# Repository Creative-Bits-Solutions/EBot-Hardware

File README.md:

# EBot-Hardware
EBot is a DIY ecosystem developed for students, kids, artists, and robotics enthusiasts to learn, explore and build working prototypes through experiments and games. Entire system includes an electronic development board with wide range of compactable sensors, graphical programming software based on Google Blockly, bunch of wheels, gears, motors, shafts and plastics, books and study materials that help to learn all basic concepts of mechanical designing, programing and electronic prototyping

We focus on STEM education to improve imagination, reasoning, analytical thinking and problem solving skills of kids. Let them Play, Make and Learn with EBot system.

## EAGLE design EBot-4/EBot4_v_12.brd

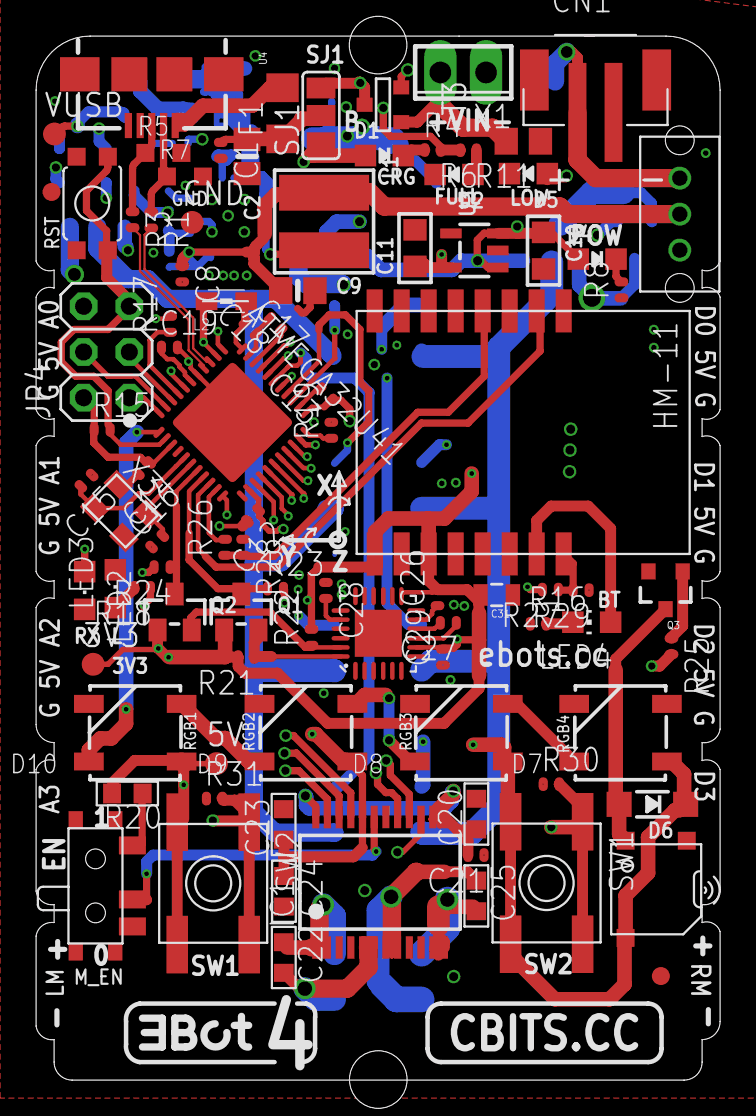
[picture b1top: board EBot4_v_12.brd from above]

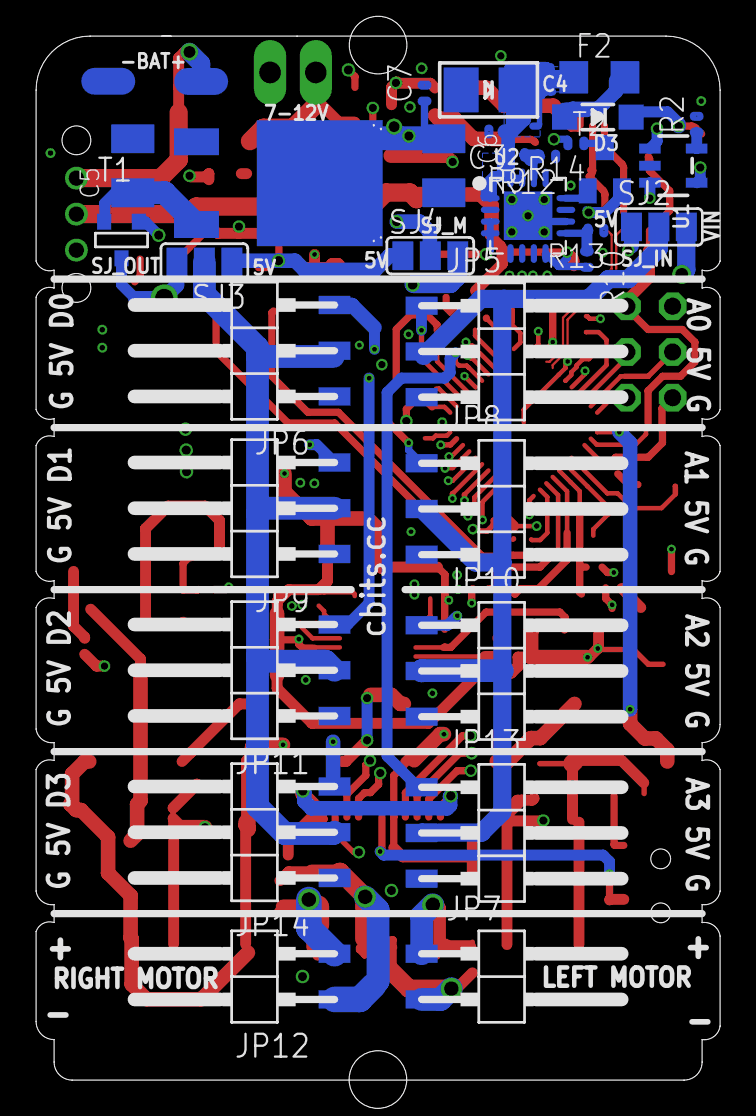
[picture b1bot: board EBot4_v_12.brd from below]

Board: 4 copper layers, 38.0 x 58.0 mm, 126 parts (33 on the bottom side), 84 nets.

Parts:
3V3, 5V: TPB1,27; B1,27
ATMEGA32U41: ATMEGA32U4-XUMU; QFN44ML7X7
AZ1084C1: AZ1084C
C1, C7, C12, C13, C14, C18: 100n; C0402
C2: 4.7µF; 0805-NO
C3: 2.2uF; C0402
C4: 100uF/6V; EIA3528-21/B-R
C5, C6: 22u; SMC_B
C8, C21, C26, C27: 0.1uF; C0402
C9: 10uF; 0805-NO
C10, C11: 10µF; _0805
C15, C16: 22pF; C0402
C17, C19: 1uF; C0402
C20, C23: 10uf; C0603
C22, C25: 0.1u; C0603
C24: 0.1uf; C0603
C28: 2.2nF; C0402
C29: 10nF; C0402
C31: 0.1uF; 0805
CN1: JST-PH-2-SMT
D1: YELLOW; CHIPLED_0805_NOOUTLINE
D2: GREEN; CHIPLED_0805_NOOUTLINE
D3, D6: MBR120; SOD-123
D4: red; CHIPLED_0805_NOOUTLINE
D5: RED; CHIPLED_0805_NOOUTLINE
D7, D8, D9, D10: WS2812B
EBOT_LOGO2: EBOT_NAME_6MM
F1, F2: 500mA; R1206
GND: TPB1,27; B1,27
HM-111: HM-11
IC1: TB6612FNG; SSOP24
JP2, JP3: FIDUCIAL1X2; FIDUCIAL-1X2
JP4: 3x2M; 2X03
JP5, JP6, JP8, JP9, JP10, JP11, JP13, JP14: 1X03SMD/90
JP7, JP12: 1X02SMD/90
KMR1: KMR7
L1: VLC5045-6.8uH; INDUCTOR_5X5MM_TDK_VLC5045
L2: MH2029-300Y; 0805
LED2: yellow; CHIPLED_0805
LED3: BLUE; CHIPLED_0805
LED4: CHIP-LED0805
MPU-60501: MPU-6050-1; QFN-24-4MM2
ON_OFF_SLIDE1: OS102011MA1QN1
Q1, Q2: BSS138; SOT23-WIDE@1
Q3: 2222A; SOT23-3
R1, R3: 22R; R0402
R2, R28, R29: 2K; R0402
R4: 470; R0402
R5, R7: CG0603MLC-05E; CT/CN0603
R6, R17, R18, R26, R27, R30, R31: 1K; R0402
R8, R14: 1k; R0402
R9, R10: 1.87M; R0402
R11: 10k; R0805
R12: 200K; R0402
R13: 340K; R0402
R15, R19, R21, R22, R23, R24: 10K; R0402
R16: 330; R0402
R20: 10K; R0603
R25: 270; R0402
SJ1, SJ2, SJ3, SJ4: SJ_2
SK-12C04051: SK-12C0405
SPK1: SMT-0540-S-R
SW1, SW2: SPST_TACT-EVQQ2; EVQ-Q2
T1: PMV48XP; SOT-23
T2: MMUN2133LT1G; SC59-BEC
T3: FDN340P/PMV48XP; SOT-23
U1: MCP73831T-2ACI/OT; SOT23-5
U2: TPS61030RSAR; PVQFN-16
U3: RT9193; SOT23-5@1
U4: USB-AB-MICRO-SMD
U$1, U$2: BATCON
VUSB: TPB1,27; B1,27
X1: 2POL254
X3: 16MHz KX-7; CRYSTAL-3.2-2.5

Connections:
+3V3: 3V3.TP, C11.1, C26.2, C29.2, C31.2, HM-111.RESETB, HM-111.VCC, MPU-60501.8, MPU-60501.13, Q1.1, Q2.1, R21.2, R22.2, U3.5
+5V: 5V.TP, ATMEGA32U41.2, ATMEGA32U41.14, ATMEGA32U41.24, ATMEGA32U41.34, AZ1084C1.VOUT, C6.+, C7.1, C10.1, C12.1, C13.1, C14.1, C23.1, C24.1, D4.A, D6.C, D7.1, D8.1, D9.1, D10.1, IC1.20, JP4.2, L2.1, R15.1, R20.2, R23.2, R24.2, SJ2.1, SJ3.1, SJ4.1, SPK1.-, SW1.A, SW1.A', SW2.A, SW2.A', T1.3, T3.2, U3.1, U3.3
A0: ATMEGA32U41.36, JP5.1
A1: ATMEGA32U41.37, JP8.1
A2: ATMEGA32U41.38, JP10.1
A3: ATMEGA32U41.39, JP13.1
A4: ATMEGA32U41.40, JP11.3
A5: ATMEGA32U41.41, JP14.3
AO1': C22.1, IC1.1, IC1.2, JP7.1
AO2': C22.2, IC1.5, IC1.6, JP7.2
AREF: ATMEGA32U41.42, C18.1
AVCC: ATMEGA32U41.44, C17.1, L2.2
BLE_KEY: HM-111.PIO0, R27.1, R29.2
BLE_LED: HM-111.PIO1, LED4.A
BO1': C25.2, IC1.11, IC1.12, JP12.2
BO2': C25.1, IC1.7, IC1.8, JP12.1
D0/RX: ATMEGA32U41.20, HM-111.UART_TX
D1/TX: ATMEGA32U41.21, R26.2
D4/M1: ATMEGA32U41.25, IC1.22
D5*/PWM2: ATMEGA32U41.31, IC1.15
D6*/PWM1: ATMEGA32U41.27, IC1.23
D7: ATMEGA32U41.1, JP9.3
D+: R3.1, R5.1, U4.D+
D-: R1.1, R7.1, U4.D-
GND: ATMEGA32U41.5, ATMEGA32U41.15, ATMEGA32U41.23, ATMEGA32U41.35, ATMEGA32U41.43, ATMEGA32U41.EXP, AZ1084C1.GND, C1.2, C2.2, C3.2, C4.-, C5.-, C6.-, C7.2, C8.2, C9.2, C10.2, C11.2, C12.2, C13.2, C14.2, C15.1, C16.1, C17.2, C18.2, C19.2, C20.2, C21.1, C23.2, C24.2, C26.1, C27.1, C28.1, C29.1, C31.1, CN1.2, D2.C, D5.C, D7.3, D8.3, D9.3, D10.3, GND.TP, HM-111.GND, IC1.3, IC1.4, IC1.9, IC1.10, IC1.18, JP4.6, JP5.3, JP6.1, JP8.3, JP9.1, JP10.3, JP11.1, JP13.3, JP14.1, KMR1.P$1, KMR1.P$2, LED2.C, LED3.C, MPU-60501.1, MPU-60501.9, MPU-60501.11, MPU-60501.18, Q3.2, R2.2, R5.2, R7.2, R8.1, R11.1, R12.1, R13.1, R16.1, R19.2, R28.1, R29.1, R30.1, R31.1, SK-12C04051.R, U1.2, U2.5, U2.6, U2.7, U2.10, U2.13, U2.P$18, U2.P$19, U2.P$20, U2.P$21, U2.P$22, U2.THERMAL, U3.2, U4.GND, U$2.P$1, X1.1, X3.2, X3.4
HWB: ATMEGA32U41.33, R19.1
IO8: ATMEGA32U41.28, JP6.3
IO9*/M3: ATMEGA32U41.29, IC1.17
IO10*: ATMEGA32U41.30, R25.2
IO11*/RGB: ATMEGA32U41.12, D10.4
IO12*/M4: ATMEGA32U41.26, IC1.21
IO13*: ATMEGA32U41.32, R18.1
LBI: R10.1, R13.2, U2.9
LBO: T2.B, U2.12
M2: ATMEGA32U41.22, IC1.16
MISO: ATMEGA32U41.11, JP4.1, R30.2, SW1.B, SW1.B'
MOSI: ATMEGA32U41.10, JP4.4, R31.2, SW2.B, SW2.B'
unnamed: D1.A, SJ1.1, U1.4
unnamed: LED2.A, R17.2
unnamed: C8.1, C9.1, L1.P$1, ON_OFF_SLIDE1.P$2, R10.2, U2.8
unnamed: LED3.A, R18.2
unnamed: D9.4, D10.2
unnamed: D1.C, R4.1
unnamed: D8.4, D9.2
unnamed: HM-111.UART_RX, R26.1, R28.2
unnamed: JP5.2, JP8.2, JP10.2, JP13.2, SJ2.2
unnamed: C28.2, MPU-60501.20
unnamed: C27.2, MPU-60501.10
unnamed: D7.4, D8.2
unnamed: LED4.C, R16.2
unnamed: R4.2, R6.2, U1.1
unnamed: R2.1, U1.5
unnamed: D2.A, R6.1
unnamed: L1.P$2, U2.3, U2.4
unnamed: D4.C, R8.2
unnamed: D5.A, R14.2
unnamed: R14.1, T2.C
unnamed: D3.A, F2.2
unnamed: JP6.2, JP9.2, JP11.2, JP14.2, SJ3.2
unnamed: Q3.1, R25.1
unnamed: F1.2, U4.VBUS
unnamed: C1.1, C2.1, F1.1, SJ1.2
unnamed: R9.1, R12.2, U2.14
unnamed: D6.A, Q3.3, SPK1.+
unnamed: AZ1084C1.VIN, C5.+, T1.2
unnamed: C20.1, C21.2, IC1.13, IC1.14, IC1.24, SJ4.2
unnamed: R20.1, SK-12C04051.L
RD_N: ATMEGA32U41.3, R1.2
RD_P: ATMEGA32U41.4, R3.2
RESET: ATMEGA32U41.13, JP4.5, KMR1.P$3, KMR1.P$4, R15.2
RXLED/SS: ATMEGA32U41.8, R17.1
SCK: ATMEGA32U41.9, JP4.3, R27.2
SCL_3V: MPU-60501.23, Q2.2, R22.1
SCL_5V: ATMEGA32U41.18, Q2.3, R24.1
SDA_3V: MPU-60501.24, Q1.2, R21.1
SDA_5V: ATMEGA32U41.19, Q1.3, R23.1
STBY: IC1.19, SK-12C04051.M
UCAP: ATMEGA32U41.6, C19.1
V+: CN1.1, ON_OFF_SLIDE1.P$3, U1.3, U$1.P$1
VDD: R11.2, SJ2.3, SJ3.3, SJ4.3, T1.1, T3.3, X1.2
VOUT1: C3.1, C4.+, F2.1, R9.2, U2.1, U2.15, U2.16
VUSB: ATMEGA32U41.7, D3.C, SJ1.3, T3.1, VUSB.TP
XTAL1: ATMEGA32U41.17, C16.2, X3.3
XTAL2: ATMEGA32U41.16, C15.2, X3.1

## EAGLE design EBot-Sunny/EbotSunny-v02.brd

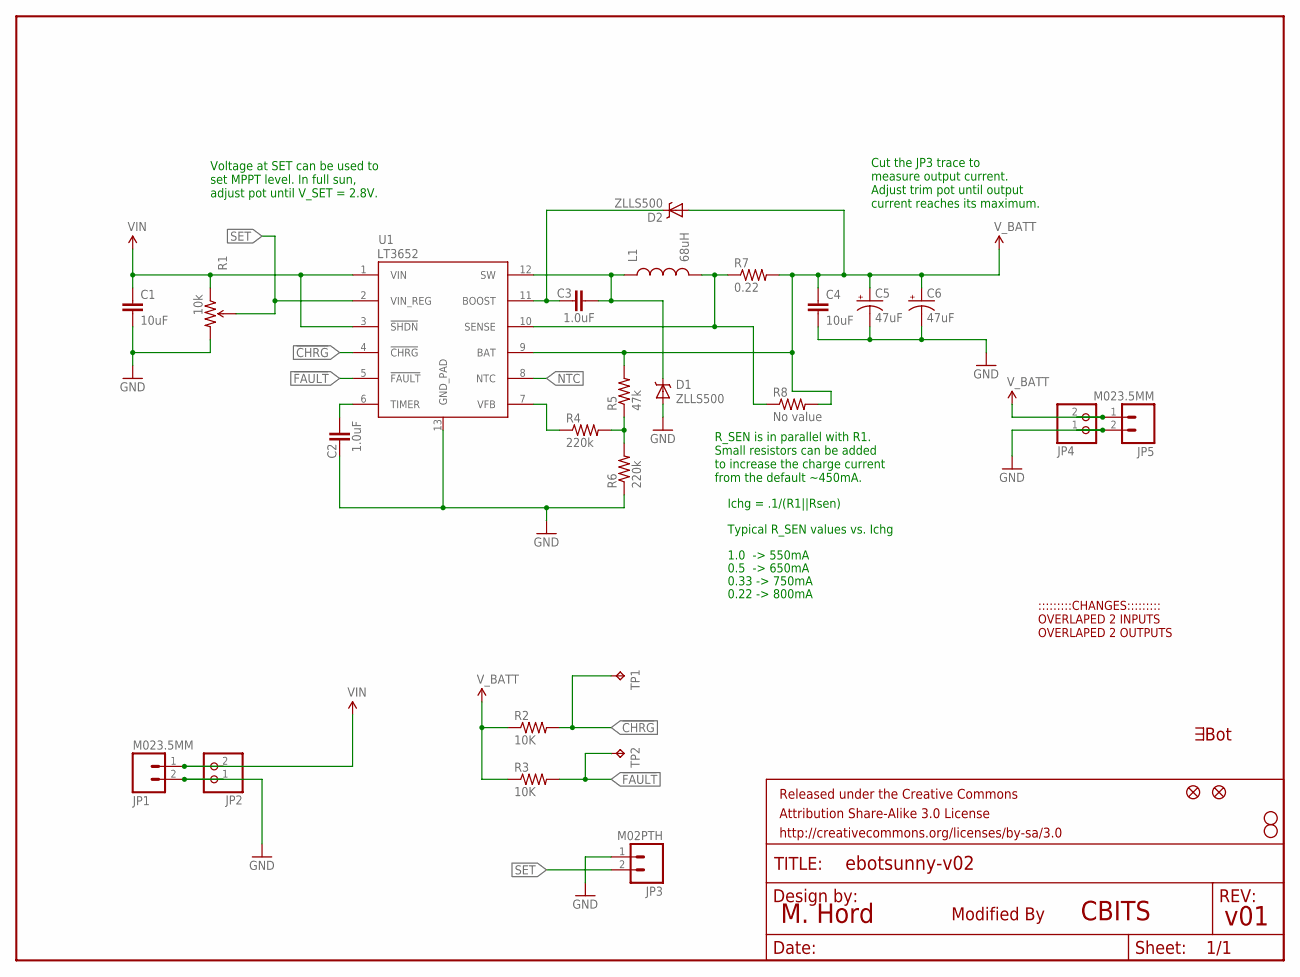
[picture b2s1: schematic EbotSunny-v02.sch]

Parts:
C1: 10uF; 1210
C2, C3: 1.0uF; 0603-CAP
C4: 10uF; 1206
C5, C6: 47uF; EIA3528
D1, D2: ZLLS500; SOT23
EBOT_LOGO3: EBOT_NAME_6MM
FID1, FID2: FIDUCIAL1X2; FIDUCIAL-1X2
FRAME1: FRAME-LETTER; CREATIVE_COMMONS
JP1, JP5: M023.5MM; SCREWTERMINAL-3.5MM-2
JP2, JP4: PINHD-1X2; 1X02
JP3: M02PTH; 1X02
L1: 68uH; CR75
R1: 10k; TRIMPOT-3MM
R2, R3: 10K; 0603-RES
R4, R6: 220k; 0603-RES
R5: 47k; 0603-RES
R7: 0.22; 0805
R8: No value; 0805
STANDOFF1, STANDOFF2: STAND-OFF
TP1, TP2: TPB1,27; B1,27
U1: LT3652; MSOP-12_GND

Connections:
!CHRG: R2.2, TP1.TP, U1.4 (!CHRG)
!FAULT: R3.2, TP2.TP, U1.5 (!FAULT)
BOOST: C3.1, D2.3 (C), U1.11 (BOOST)
FB: R4.2, R5.1, R6.2
GND: C1.2, C2.1, C4.2, C5.C (-), C6.C (-), D1.1 (A), JP1.2, JP2.1, JP3.1, JP4.1, JP5.2, R1.3 (CW), R6.1, U1.13 (GND_PAD)
unnamed: R4.1, U1.7 (VFB)
NTC: U1.8 (NTC)
SENSE: L1.P$2 (2), R7.1, R8.1, U1.10 (SENSE)
SET: JP3.2, R1.2 (WIPER), U1.2 (VIN_REG)
SW: C3.2, D1.3 (C), L1.P$1 (1), U1.12 (SW)
TIMER: C2.2, U1.6 (TIMER)
VIN: C1.1, JP1.1, JP2.2, R1.1 (CCW), U1.1 (VIN), U1.3 (!SHDN)
V_BATT: C4.1, C5.A (+), C6.A (+), D2.1 (A), JP4.2, JP5.1, R2.1, R3.1, R5.2, R7.2, R8.2, U1.9 (BAT)

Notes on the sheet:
Cut the JP3 trace to measure output current. Adjust trim pot until output current reaches its maximum.
R_SEN is in parallel with R1. Small resistors can be added to increase the charge current from the default ~450mA.
0.22 -> 800mA
Ichg = .1/(R1||Rsen)
Typical R_SEN values vs. Ichg
1.0 -> 550mA
0.33 -> 750mA
0.5 -> 650mA
Voltage at SET can be used to set MPPT level. In full sun, adjust pot until V_SET = 2.8V.
v01
M. Hord
CBITS
Modified By
:::::::::CHANGES::::::::: OVERLAPED 2 INPUTS OVERLAPED 2 OUTPUTS

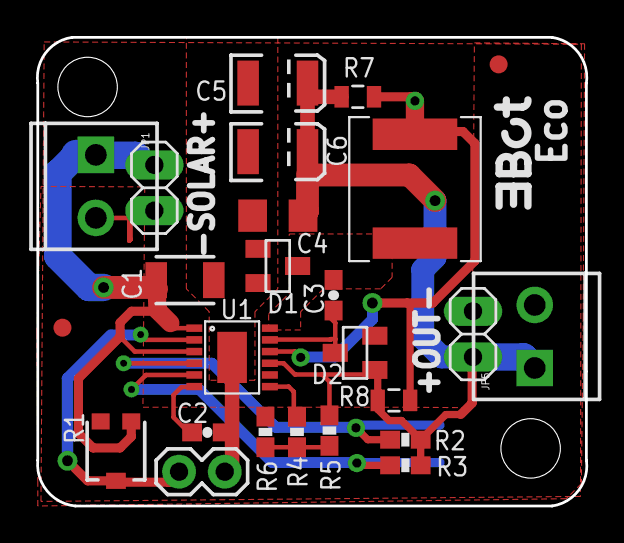
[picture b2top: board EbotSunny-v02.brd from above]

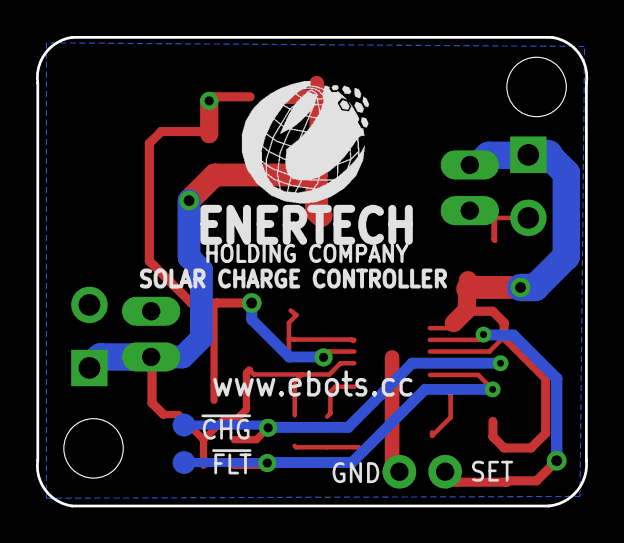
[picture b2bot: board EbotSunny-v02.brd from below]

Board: 2 copper layers, 30.5 x 26.0 mm, 31 parts (2 on the bottom side), 12 nets.

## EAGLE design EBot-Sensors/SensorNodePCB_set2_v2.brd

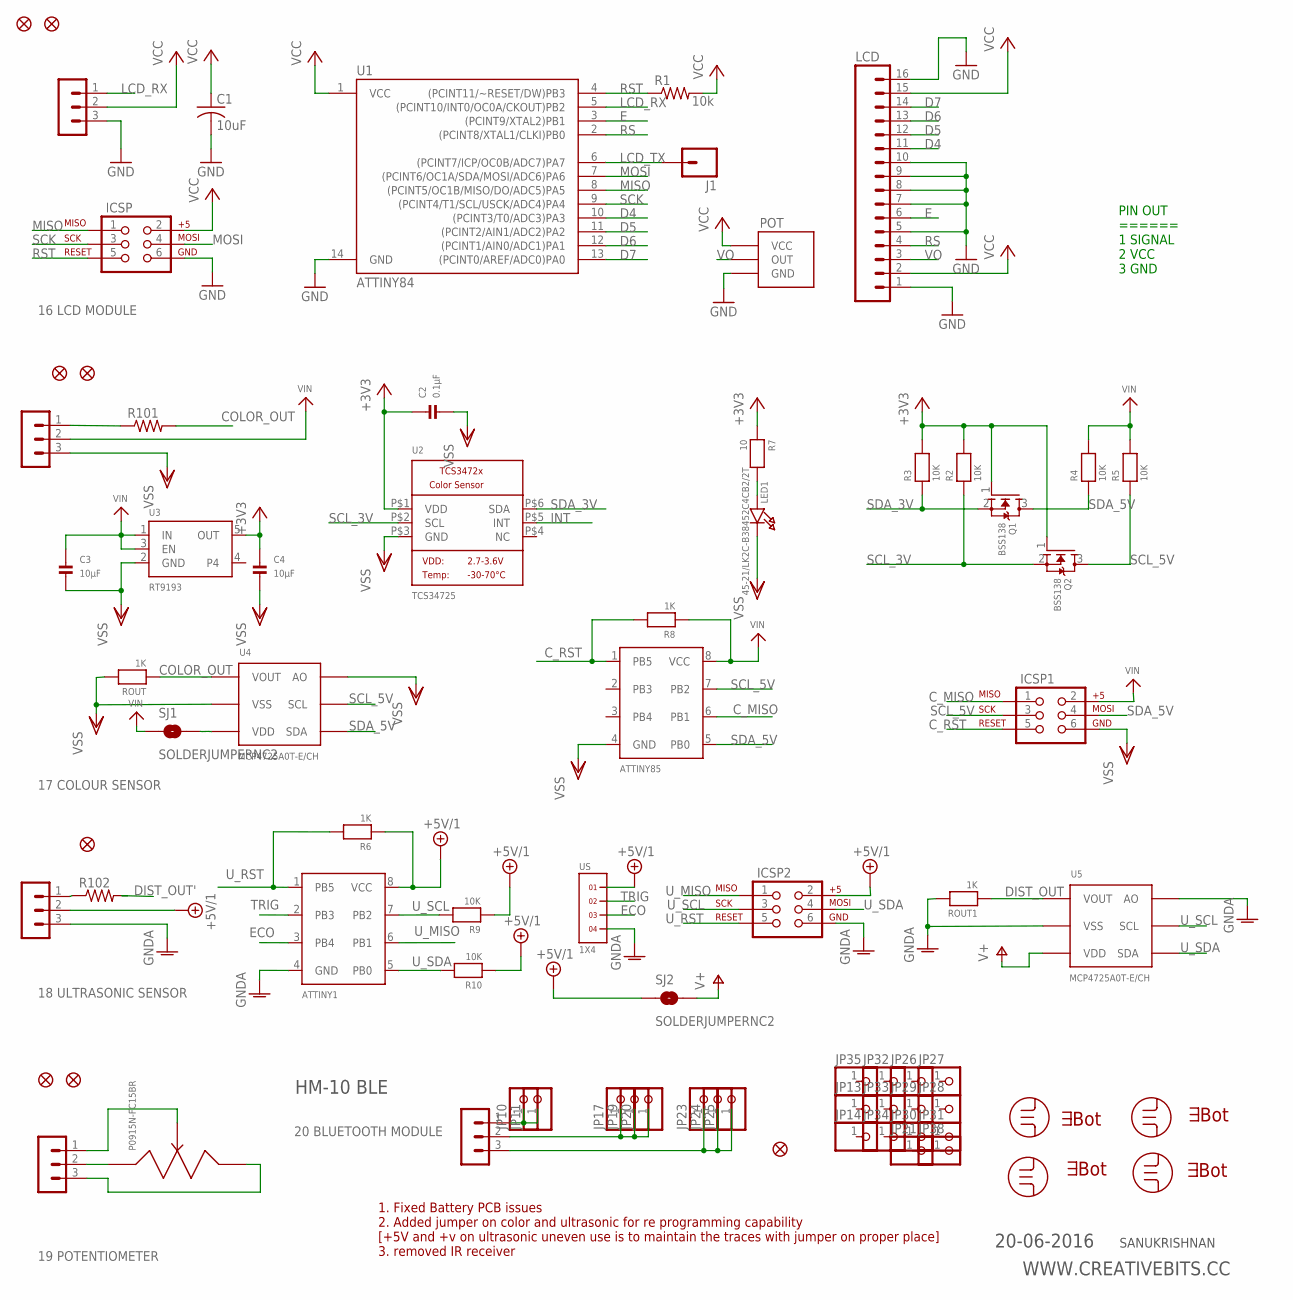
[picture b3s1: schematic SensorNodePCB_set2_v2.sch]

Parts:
ATTINY1, ATTINY85: ATTINY45; SOIC8
C1: 10uF; C1206
C2: 0.1µF; _0805
C3, C4: 10µF; _0805
COLORSENSOR: MA03-1
ICSP, ICSP1, ICSP2: AVR_SPI_PRG_6NS; 2X3-NS
J1: M01NOSILK-KIT; 1X01NS-KIT
JP1, JP2, JP4, JP6, JP9, JP12, JP15, JP18: FIDUCIAL1X2; FIDUCIAL-1X2
JP10, JP11, JP13, JP14, JP17, JP19, JP20, JP21, JP23, JP24, JP25, JP26, JP27, JP28, JP29, JP30, JP31, JP32, JP33, JP34, JP35, JP38: PINHD-1X1CB; 1X01-CLEANBIG
LCD: M16LONGPADS; 1X16_LONGPADS
LCD_NODE: MA03-1
LED1: 45-21/LK2C-B38452C4CB2/2T; EVERLIGHT_45-21
POT: TRIMMER_EVN
POT1: P0915N-FC15BR
POTENTIOMETER: MA03-1
Q1, Q2: BSS138; SOT23-WIDE
R1: 10k; M0805
R2, R3, R4, R5, R9, R10: 10K; _0805
R6, R8: 1K; _0805
R7: 10; _0805
R101, R102: R-US_M0805; M0805
ROUT, ROUT1: 1K; _0805
SJ1, SJ2: SOLDERJUMPERNC2; SJ_2S-NOTRACE
U1: ATTINY84; SO14
U2: TCS34725; TCS3472_FN6
U3: RT9193; SOT23-5
U4, U5: MCP4725
U$30, U$32, U$33, U$34: EBOT_LOGO_6MMX6MM; EBOT_6MMX6MM
U$35, U$37, U$38, U$39: EBOT_NAME_6MM
ULTRASONICSENSOR, ULTRASONICSENSOR1: MA03-1
US: 1X4

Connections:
+3V3: C2.1, C4.1, Q1.1 (G), Q2.1 (G), R2.2, R3.2, R7.1, U2.P$1 (VDD), U3.5 (OUT)
+5V/1: ATTINY1.8 (VCC), ICSP2.2, R6.1, R9.1, R10.1, SJ2.1, ULTRASONICSENSOR.2, US.1
COLOR_OUT: R101.2, ROUT.1, U4.P$1 (VOUT)
C_MISO: ATTINY85.6 (PB1), ICSP1.1
C_RST: ATTINY85.1 (PB5), ICSP1.5, R8.2
D4: LCD.11, U1.10 ((PCINT3/T0/ADC3)PA3)
D5: LCD.12, U1.11 ((PCINT2/AIN1/ADC2)PA2)
D6: LCD.13, U1.12 ((PCINT1/AIN0/ADC1)PA1)
D7: LCD.14, U1.13 ((PCINT0/AREF/ADC0)PA0)
DIST_OUT: R102.2, ROUT1.1, U5.P$1 (VOUT)
DIST_OUT': R102.1, ULTRASONICSENSOR.1
E: LCD.6, U1.3 ((PCINT9/XTAL2)PB1)
ECO: ATTINY1.3 (PB4), US.3
GND: C1.2, ICSP.6, LCD.1, LCD.5, LCD.7, LCD.8, LCD.9, LCD.10, LCD.16, LCD_NODE.3, POT.P$2 (GND), U1.14 (GND)
GNDA: ATTINY1.4 (GND), ICSP2.6, ROUT1.2, U5.P$2 (VSS), U5.P$6 (AO), ULTRASONICSENSOR.3, US.4
INT: U2.P$5 (INT)
LCD_RX: LCD_NODE.1, U1.5 ((PCINT10/INT0/OC0A/CKOUT)PB2)
LCD_TX: J1.1, U1.6 ((PCINT7/ICP/OC0B/ADC7)PA7)
MISO: ICSP.1, U1.8 ((PCINT5/OC1B/MISO/DO/ADC5)PA5)
MOSI: ICSP.4, U1.7 ((PCINT6/OC1A/SDA/MOSI/ADC6)PA6)
unnamed: LED1.A, R7.2
unnamed: POT1.VCC, POTENTIOMETER.2
unnamed: SJ1.2, U4.P$3 (VDD)
unnamed: COLORSENSOR.1, R101.1
unnamed: POT1.GND, POTENTIOMETER.3
unnamed: JP10.1, JP11.1, ULTRASONICSENSOR1.1
unnamed: JP17.1, JP19.1, JP20.1, ULTRASONICSENSOR1.2
unnamed: JP23.1, JP24.1, JP25.1, ULTRASONICSENSOR1.3
POT_OUT: POT1.OUT, POTENTIOMETER.1
RS: LCD.4, U1.2 ((PCINT8/XTAL1/CLKI)PB0)
RST: ICSP.5, R1.1, U1.4 ((PCINT11/~RESET/DW)PB3)
SCK: ICSP.3, U1.9 ((PCINT4/T1/SCL/USCK/ADC4)PA4)
SCL_3V: Q2.2 (S), R2.1, U2.P$2 (SCL)
SCL_5V: ATTINY85.7 (PB2), ICSP1.3, Q2.3 (D), R5.1, U4.P$5 (SCL)
SDA_3V: Q1.2 (S), R3.1, U2.P$6 (SDA)
SDA_5V: ATTINY85.5 (PB0), ICSP1.4, Q1.3 (D), R4.1, U4.P$4 (SDA)
TRIG: ATTINY1.2 (PB3), US.2
U_MISO: ATTINY1.6 (PB1), ICSP2.1
U_RST: ATTINY1.1 (PB5), ICSP2.5, R6.2
U_SCL: ATTINY1.7 (PB2), ICSP2.3, R9.2, U5.P$5 (SCL)
U_SDA: ATTINY1.5 (PB0), ICSP2.4, R10.2, U5.P$4 (SDA)
V+: SJ2.2, U5.P$3 (VDD)
VCC: C1.1, ICSP.2, LCD.2, LCD.15, LCD_NODE.2, POT.P$1 (VCC), R1.2, U1.1 (VCC)
VIN: ATTINY85.8 (VCC), C3.1, COLORSENSOR.2, ICSP1.2, R4.2, R5.2, R8.1, SJ1.1, U3.1 (IN), U3.3 (EN)
VO: LCD.3, POT.P$3 (OUT)
VSS: ATTINY85.4 (GND), C2.2, C3.2, C4.2, COLORSENSOR.3, ICSP1.6, LED1.K (C), ROUT.2, U2.P$3 (GND), U3.2 (GND), U4.P$2 (VSS), U4.P$6 (AO)

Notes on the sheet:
16 LCD MODULE
PIN OUT ====== 1 SIGNAL 2 VCC 3 GND
17 COLOUR SENSOR
18 ULTRASONIC SENSOR
19 POTENTIOMETER
20 BLUETOOTH MODULE
HM-10 BLE
20-06-2016
WWW.CREATIVEBITS.CC
SANUKRISHNAN
1. Fixed Battery PCB issues 2. Added jumper on color and ultrasonic for re programming capability [+5V and +v on ultrasonic uneven use is to maintain the traces with jumper on proper place] 3. removed IR receiver

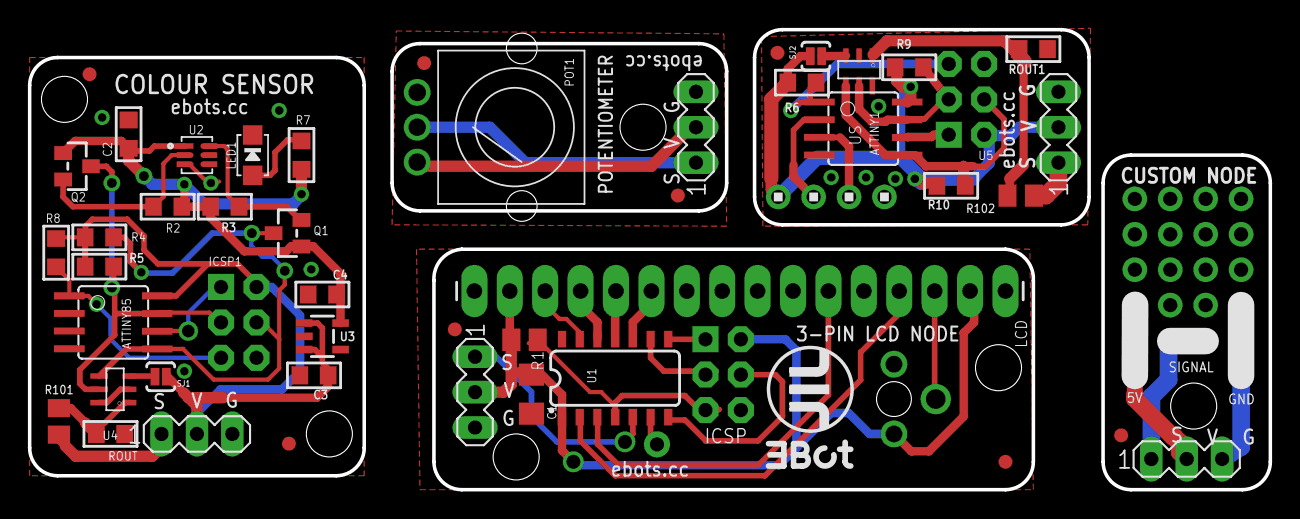
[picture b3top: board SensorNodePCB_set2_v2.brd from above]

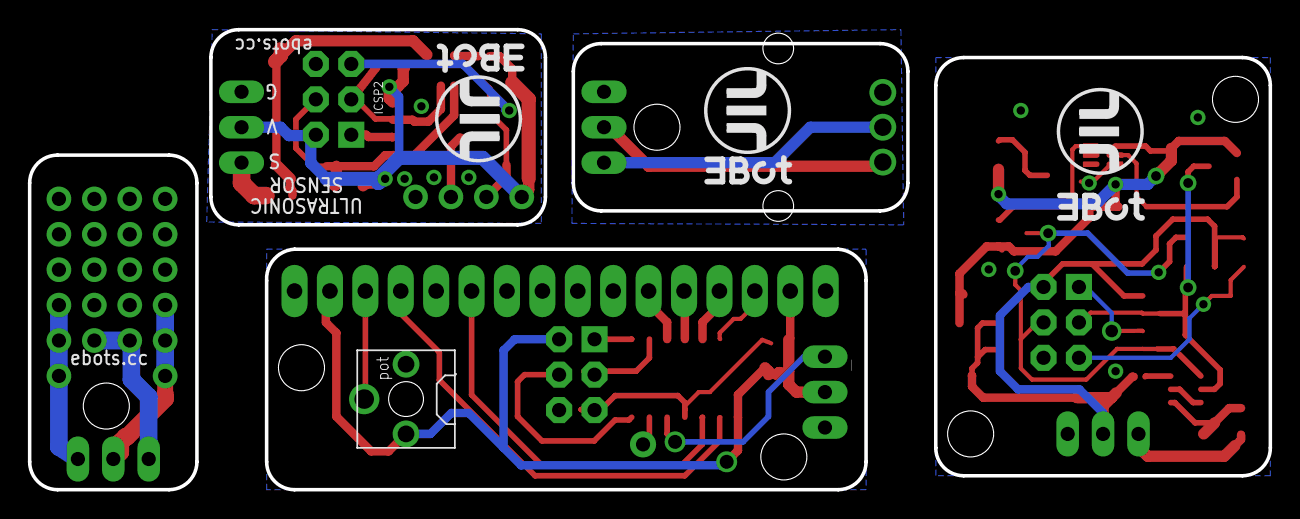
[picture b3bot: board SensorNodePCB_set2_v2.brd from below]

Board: 2 copper layers, 89.0 x 33.0 mm, 87 parts (8 on the bottom side), 45 nets.

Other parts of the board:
JP3, JP5, JP7, JP8, JP16, JP22: STAND-OFF

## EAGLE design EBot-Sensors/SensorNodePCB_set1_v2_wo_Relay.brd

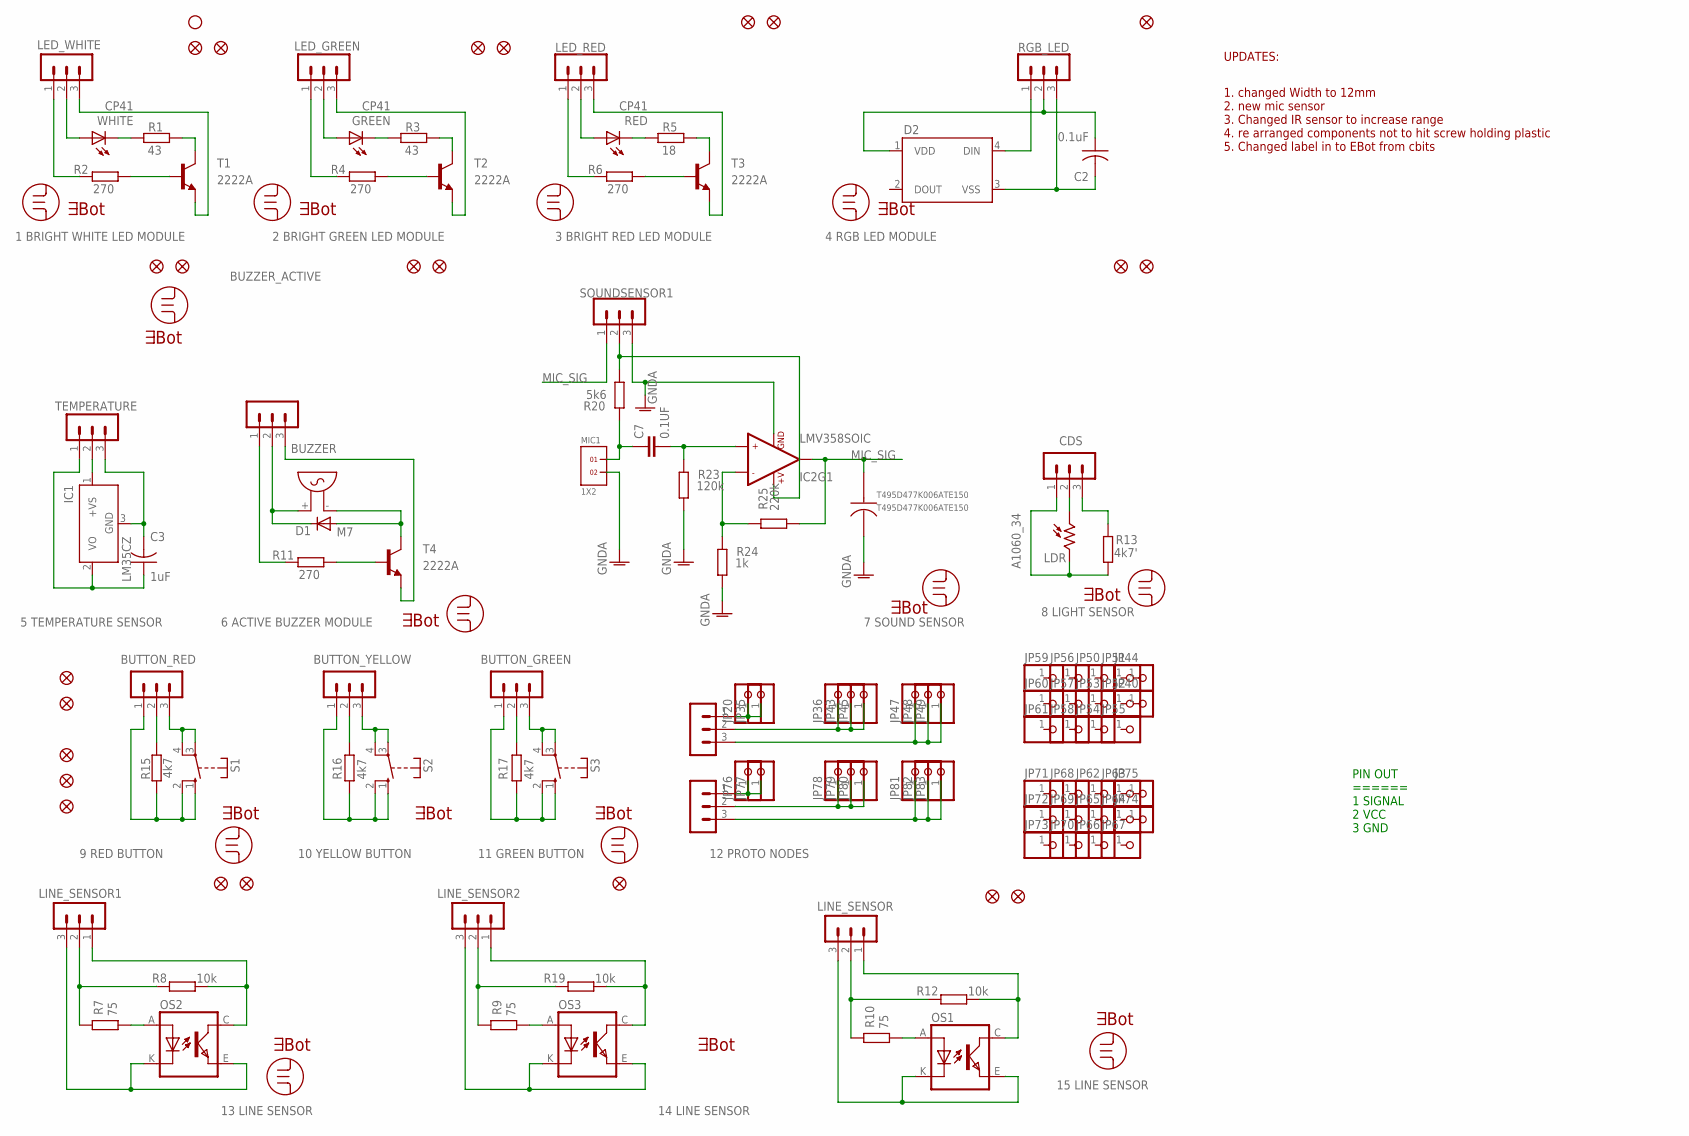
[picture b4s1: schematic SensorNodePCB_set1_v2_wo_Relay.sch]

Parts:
BUTTON_GREEN: MA03-1
BUTTON_RED: MA03-1
BUTTON_YELLOW: MA03-1
BUZZER: F/QMX
BUZZER_ACTIVE: MA03-1
C2: 0.1uF; C0805
C3: 1uF; C0805
C7: 0.1UF; 0805
CDS: MA03-1
D1: M7; DO214AC
D2: WS2812B
GREEN: CP41; CP41B
IC1: LM35CZ; TO92
IC2: LMV358SOIC; SO08
JP1: STAND-OFF
JP2, JP4, JP6, JP7, JP12, JP18, JP19, JP23, JP24, JP25, JP26, JP28, JP29, JP31, JP32, JP33, JP34, JP37, JP38, JP39, JP41, JP42, JP46: FIDUCIAL1X2; FIDUCIAL-1X2
JP20, JP35, JP36, JP40, JP43, JP44, JP45, JP47, JP48, JP49, JP50, JP51, JP52, JP53, JP54, JP55, JP56, JP57, JP58, JP59, JP60, JP61, JP62, JP63, JP64, JP65, JP66, JP67, JP68, JP69, JP70, JP71, JP72, JP73, JP74, JP75, JP76, JP77, JP78, JP79, JP80, JP81, JP82, JP83: PINHD-1X1CB; 1X01-CLEANBIG
LDR: A1060_34; T0-46-A10XX
LED_GREEN: MA03-1
LED_RED: MA03-1
LED_WHITE: MA03-1
LINE_SENSOR, LINE_SENSOR1, LINE_SENSOR2: MA03-1
MIC1: 1X2
OS1, OS2, OS3: TCRT5000
R1, R3: 43; R0805
R2, R4, R6, R11: 270; R0805
R5: 18; R0805
R7, R9, R10: 75; R0805
R8, R12, R19: 10k; R0805
R13: 4k7'; R0805
R15, R16, R17: 4k7; R0805
R20: 5k6; R0805
R23: 120k; R0805
R24: 1k; R0805
R25: 220k; R0805
RED: CP41; CP41B
RGB_LED: MA03-1
S1, S2, S3: RACON12
SOUNDSENSOR1: MA03-1
T1, T2, T3, T4: 2222A; SOT23-3
TEMPERATURE: MA03-1
U$1, U$3, U$4, U$6, U$8, U$9, U$10, U$12, U$13, U$14, U$15, U$16: EBOT_LOGO_6MMX6MM; EBOT_6MMX6MM
U$11: T495D477K006ATE150
U$17, U$18, U$20, U$21, U$22, U$23, U$24, U$25, U$26, U$27, U$29, U$30, U$31: EBOT_NAME_6MM
ULTRASONICSENSOR1, ULTRASONICSENSOR2: MA03-1
WHITE: CP41; CP41B

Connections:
GNDA: IC2.4 (GND), MIC1.2, R23.1, R24.1, SOUNDSENSOR1.3, U$11.-
MIC_SIG: IC2.1 (OUT1), R25.1, SOUNDSENSOR1.1, U$11.+
unnamed: LED_WHITE.1, R2.2
unnamed: R2.1, T1.1 (B)
unnamed: R1.2, WHITE.1 (C), WHITE.4 (C)
unnamed: R1.1, T1.3 (C)
unnamed: R4.1, T2.1 (B)
unnamed: LED_WHITE.2, WHITE.2 (A), WHITE.3 (A)
unnamed: GREEN.1 (C), GREEN.4 (C), R3.2
unnamed: LED_GREEN.1, R4.2
unnamed: R3.1, T2.3 (C)
unnamed: GREEN.2 (A), GREEN.3 (A), LED_GREEN.2
unnamed: R6.1, T3.1 (B)
unnamed: R5.2, RED.1 (C), RED.4 (C)
unnamed: LED_RED.1, R6.2
unnamed: R5.1, T3.3 (C)
unnamed: LED_RED.2, RED.2 (A), RED.3 (A)
unnamed: D2.4 (DIN), RGB_LED.1
unnamed: C2.1, D2.1 (VDD), RGB_LED.2
unnamed: C2.2, D2.3 (VSS), RGB_LED.3
unnamed: BUTTON_RED.1, R15.2, S1.1 (S), S1.2 (S)
unnamed: BUTTON_RED.2, R15.1
unnamed: BUTTON_YELLOW.1, R16.2, S2.1 (S), S2.2 (S)
unnamed: LED_WHITE.3, T1.2 (E)
unnamed: JP20.1, JP35.1, ULTRASONICSENSOR1.1
unnamed: R11.1, T4.1 (B)
unnamed: LED_GREEN.3, T2.2 (E)
unnamed: LED_RED.3, T3.2 (E)
unnamed: IC1.1 (+VS), TEMPERATURE.2
unnamed: BUZZER_ACTIVE.1, R11.2
unnamed: BUZZER.- (1), D1.A, T4.3 (C)
unnamed: BUZZER.+ (2), BUZZER_ACTIVE.2, D1.C
unnamed: BUZZER_ACTIVE.3, T4.2 (E)
unnamed: C3.2, IC1.3 (GND), TEMPERATURE.3
unnamed: C3.1, IC1.2 (VO), TEMPERATURE.1
unnamed: LINE_SENSOR.3, OS1.E (EMITTER), OS1.K (CATHODE)
unnamed: LINE_SENSOR.2, R10.1, R12.1
unnamed: OS1.A (ANODE), R10.2
unnamed: CDS.1, LDR.2, R13.2
unnamed: CDS.2, LDR.1
unnamed: CDS.3, R13.1
unnamed: LINE_SENSOR.1, OS1.C (COLLECTOR), R12.2
unnamed: JP36.1, JP43.1, JP45.1, ULTRASONICSENSOR1.2
unnamed: JP47.1, JP48.1, JP49.1, ULTRASONICSENSOR1.3
unnamed: JP76.1, JP77.1, ULTRASONICSENSOR2.1
unnamed: BUTTON_GREEN.1, R17.2, S3.1 (S), S3.2 (S)
unnamed: BUTTON_GREEN.3, S3.3, S3.4
unnamed: JP78.1, JP79.1, JP80.1, ULTRASONICSENSOR2.2
unnamed: BUTTON_YELLOW.2, R16.1
unnamed: JP81.1, JP82.1, JP83.1, ULTRASONICSENSOR2.3
unnamed: BUTTON_GREEN.2, R17.1
unnamed: LINE_SENSOR1.3, OS2.E (EMITTER), OS2.K (CATHODE)
unnamed: LINE_SENSOR1.2, R7.1, R8.1
unnamed: LINE_SENSOR1.1, OS2.C (COLLECTOR), R8.2
unnamed: OS2.A (ANODE), R7.2
unnamed: LINE_SENSOR2.3, OS3.E (EMITTER), OS3.K (CATHODE)
unnamed: LINE_SENSOR2.2, R9.1, R19.1
unnamed: LINE_SENSOR2.1, OS3.C (COLLECTOR), R19.2
unnamed: OS3.A (ANODE), R9.2
unnamed: BUTTON_YELLOW.3, S2.3, S2.4
unnamed: IC2.8 (+V), R20.1, SOUNDSENSOR1.2
unnamed: C7.1, MIC1.1, R20.2
unnamed: BUTTON_RED.3, S1.3, S1.4
unnamed: C7.2, IC2.3 (+IN1), R23.2
unnamed: IC2.2 (-IN1), R24.2, R25.2

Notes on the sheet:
1 BRIGHT WHITE LED MODULE
2 BRIGHT GREEN LED MODULE
3 BRIGHT RED LED MODULE
4 RGB LED MODULE
6 ACTIVE BUZZER MODULE
5 TEMPERATURE SENSOR
8 LIGHT SENSOR
7 SOUND SENSOR
PIN OUT ====== 1 SIGNAL 2 VCC 3 GND
9 RED BUTTON
10 YELLOW BUTTON
11 GREEN BUTTON
12 PROTO NODES
13 LINE SENSOR
14 LINE SENSOR
15 LINE SENSOR
UPDATES:
1. changed Width to 12mm 2. new mic sensor 3. Changed IR sensor to increase range 4. re arranged components not to hit screw holding plastic 5. Changed label in to EBot from cbits

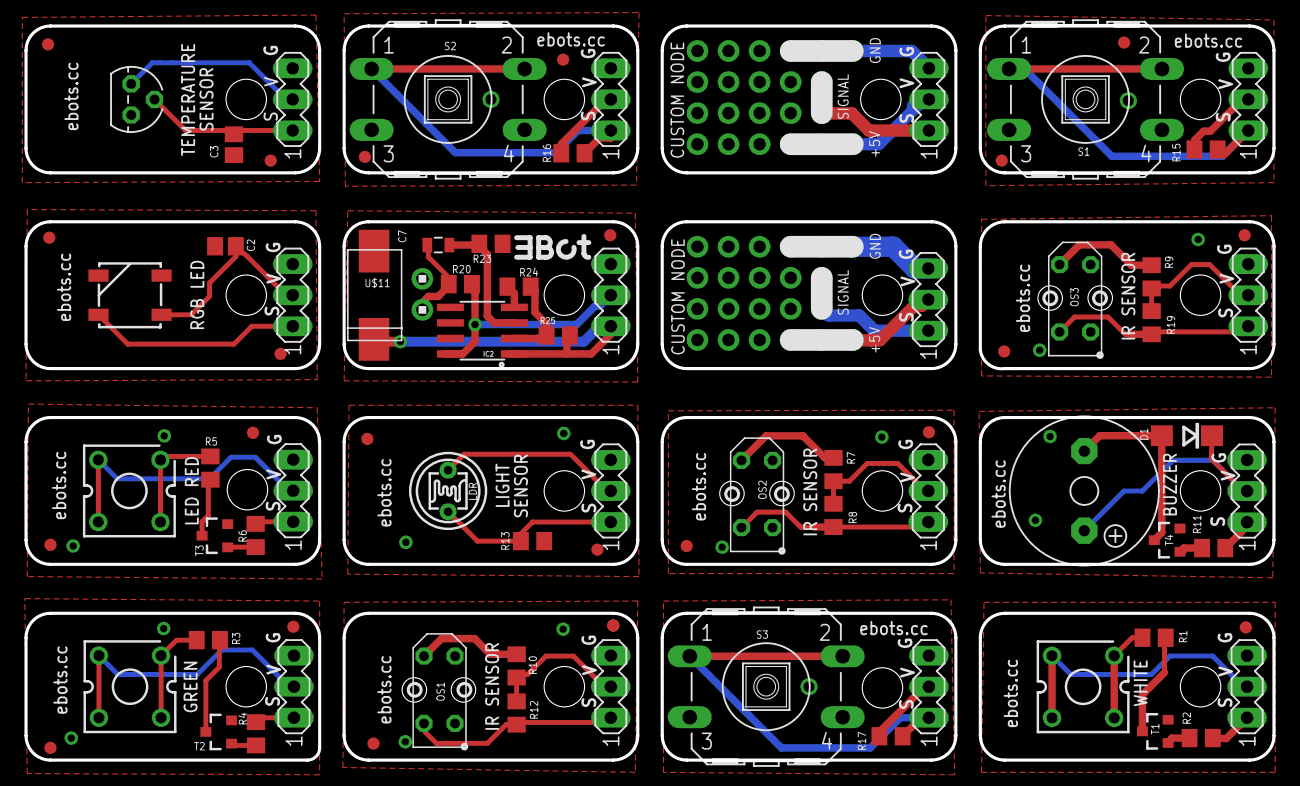
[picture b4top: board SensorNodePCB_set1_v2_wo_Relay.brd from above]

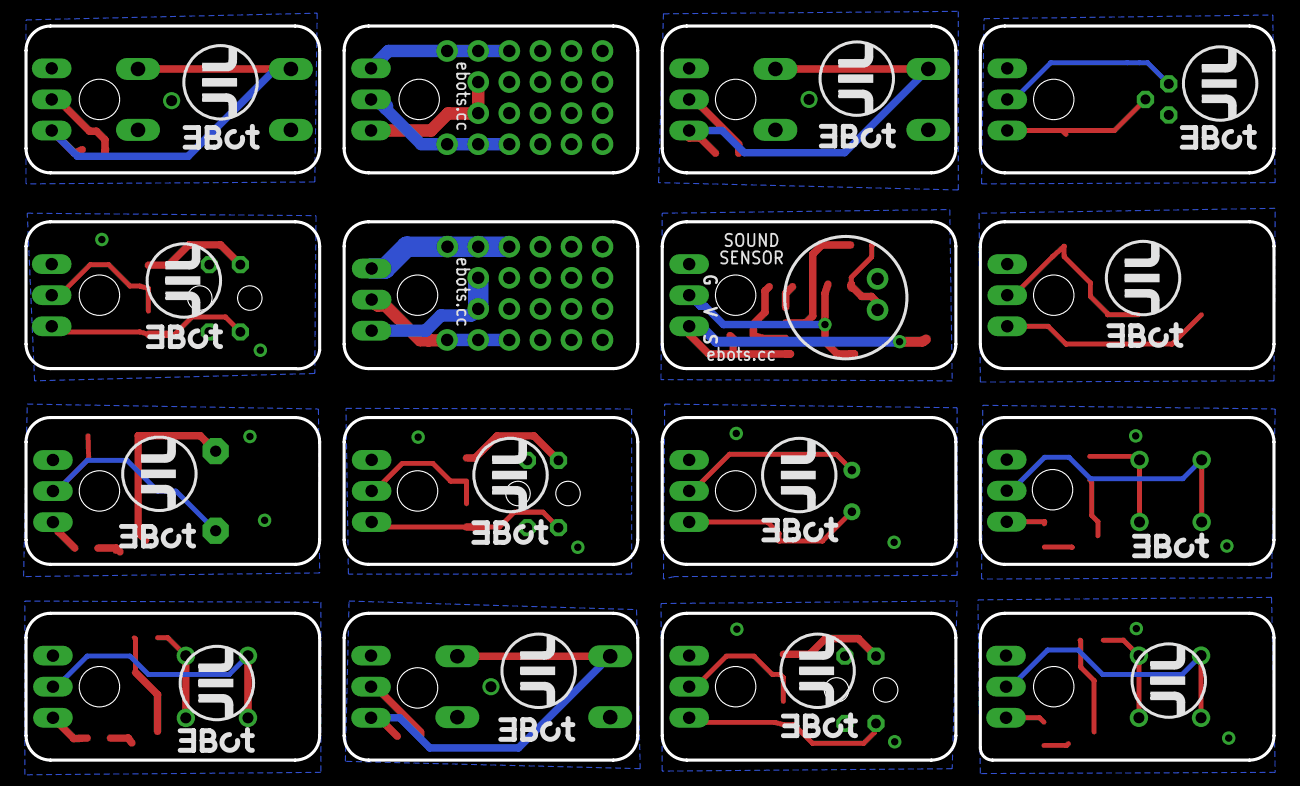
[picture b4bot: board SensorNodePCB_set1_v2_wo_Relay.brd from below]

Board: 2 copper layers, 102.0 x 60.0 mm, 169 parts (24 on the bottom side), 65 nets.

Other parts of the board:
JP3, JP5, JP8, JP9, JP10, JP11, JP13, JP14, JP15, JP16, JP17, JP21, JP22, JP27, JP30: STAND-OFF

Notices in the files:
parts and their libraries:
microbuilder: This work is placed in the public domain, and may be freely used for commercial and non-commercial work with the following conditions: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
SparkFun-DiscreteSemi: Licensing: Creative Commons ShareAlike 4.0 International - https://creativecommons.org/licenses/by-sa/4.0
